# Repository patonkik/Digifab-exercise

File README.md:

# Digifab-exercise
This repository includes the files associated with the Principles of Digital Fabrication project of Valtteri Kuosmanen, Toni Kontu and Tuukka Veteli.

It includes the following files:
- Eagle design files for the PCB
- Final image files for the PCB milling machine
- Vector graphics files for the 2D-models used in the project
- Source code for the Arduino Uno circuit
- The Bill of Materials for the project
- This Readme file

The reports for the project are stored in Google Drive, so we have provided links here to access them:
- Diary report: https://docs.google.com/document/d/1O5RGzFHKtEPdaIsV6PFCcRubVUHT45-Og6ERZvJMx08/edit?usp=sharing
- Introductory report: https://docs.google.com/document/d/1czEiMWIs1GIEoo9ajx7ruvBawDhYcQw6cwD3k_GDKVw/edit?usp=sharing
- Summary report: https://docs.google.com/document/d/19Vfl5VsGo5zwWBFI96ErdCJB0PnRMdfwJGnuuE-HRK0/edit?usp=sharing
- Final presentation: https://docs.google.com/presentation/d/1g4eWnZzMv_NSO_lvLBR8bk_6Fv4PtjN5TDbLw8TsR_Y/edit?usp=sharing

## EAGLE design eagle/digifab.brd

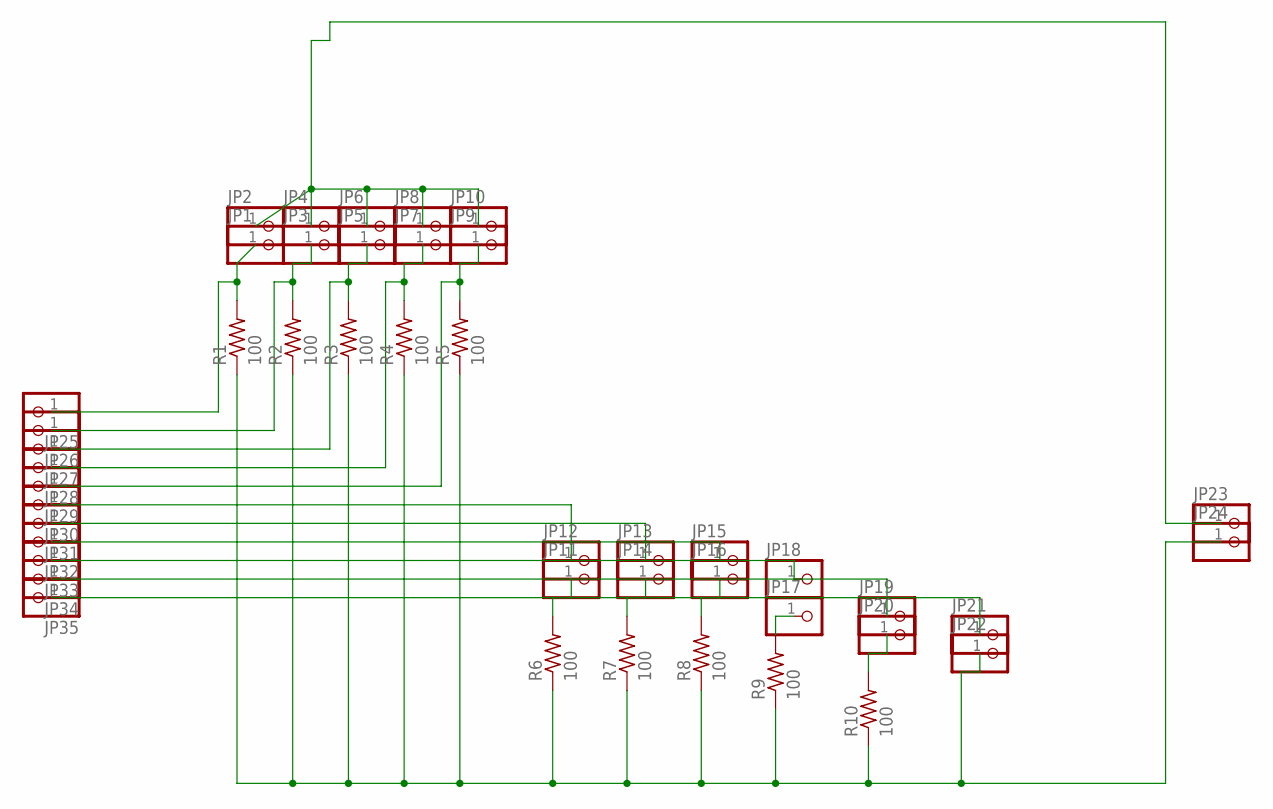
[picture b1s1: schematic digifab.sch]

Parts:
JP1, JP2, JP3, JP4, JP5, JP6, JP7, JP8, JP9, JP10, JP11, JP12, JP13, JP14, JP15, JP16, JP17, JP18, JP19, JP20, JP21, JP22, JP23, JP24, JP25, JP26, JP27, JP28, JP29, JP30, JP31, JP32, JP33, JP34, JP35: PINHD-1X01_2.54-90°; 1X01/90
R1, R2, R3, R4, R5, R6, R7, R8, R9, R10: 100; R1206FAB

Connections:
unnamed: JP1.1, JP25.1, R1.2
unnamed: JP3.1, JP26.1, R2.2
unnamed: JP5.1, JP27.1, R3.2
unnamed: JP7.1, JP28.1, R4.2
unnamed: JP9.1, JP29.1, R5.2
unnamed: JP22.1, JP24.1, R1.1, R2.1, R3.1, R4.1, R5.1, R6.1, R7.1, R8.1, R9.1, R10.1
unnamed: JP18.1, JP33.1
unnamed: JP17.1, R9.2
unnamed: JP2.1, JP4.1, JP6.1, JP8.1, JP10.1, JP23.1
unnamed: JP12.1, JP30.1
unnamed: JP13.1, JP31.1
unnamed: JP15.1, JP32.1
unnamed: JP11.1, R6.2
unnamed: JP14.1, R7.2
unnamed: JP16.1, R8.2
unnamed: JP20.1, R10.2
unnamed: JP19.1, JP34.1
unnamed: JP21.1, JP35.1

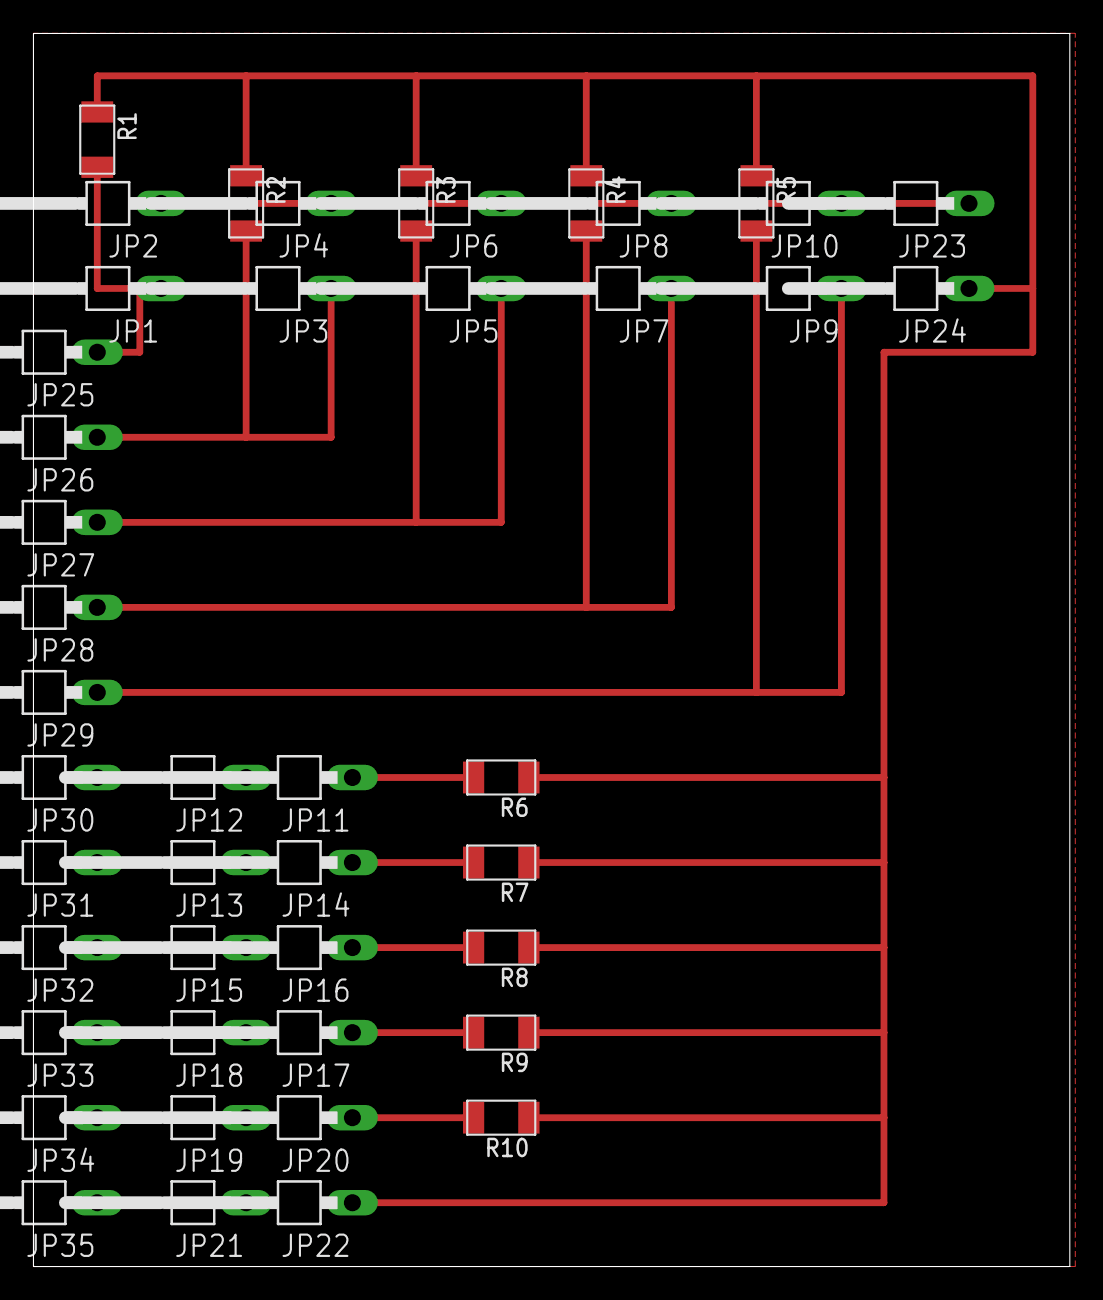
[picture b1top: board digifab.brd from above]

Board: 2 copper layers, 61.9 x 73.6 mm, 45 parts (0 on the bottom side), 18 nets.

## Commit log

2018-05-05 Create muistipeli
2018-05-05 Update muistipeli
2018-05-05 Create Piippaus+moottori
2018-05-05 Update Piippaus+moottori
2018-05-07 Eagle design files and final board layouts, vector graphics for 2D-models
2018-05-07 Added Bill of Materials
2018-05-07 Update muistipeli
    en saa ottamaan inputteja tossa itse pelissä
2018-05-07 Update muistipeli
    täysin toimiva. koitan vielä muokkailla semmoseksi että moottori pyörii ja piippaus kuuluu koko ajan eikä vaan arvausta tehdessä
2018-05-07 Update muistipeli
    äänet kuuluu vain arvausta tehdessä. jos ne haluaisi toimimaan jatkuvasti niin pitäisi sotkea monta tuntia valmista koodia. Its a feature not a bug. (sori)
